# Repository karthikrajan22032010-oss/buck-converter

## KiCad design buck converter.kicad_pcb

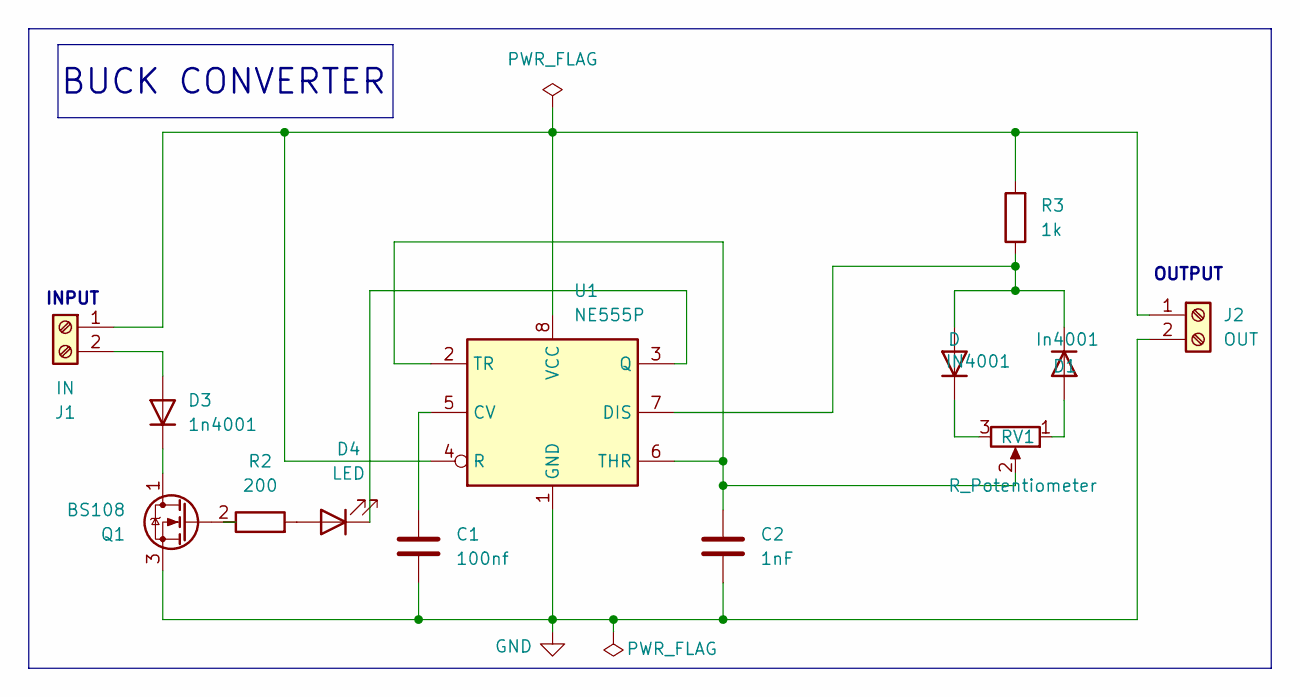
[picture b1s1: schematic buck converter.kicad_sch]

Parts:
C1: 100nf; C_Disc_D8.0mm_W5.0mm_P7.50mm
C2: 1nF; C_Disc_D8.0mm_W5.0mm_P7.50mm
D1: In4001; D_5W_P12.70mm_Horizontal
D3: 1n4001; D_5W_P12.70mm_Horizontal
D4: LED; LED_D5.0mm
IN4001: D; D_5W_P12.70mm_Horizontal
J1: IN; TerminalBlock_Phoenix_MKDS-1,5-2_1x02_P5.00mm_Horizontal
J2: OUT; TerminalBlock_Phoenix_MKDS-1,5-2_1x02_P5.00mm_Horizontal
Q1: BS108; TO-92_Inline_Wide
R2: 200; R_Axial_DIN0207_L6.3mm_D2.5mm_P7.62mm_Horizontal
R3: 1k; R_Axial_DIN0207_L6.3mm_D2.5mm_P7.62mm_Horizontal
RV1: R_Potentiometer; Potentiometer_Alps_RK09Y11_Single_Horizontal
U1: NE555P; DIP-8_W7.62mm

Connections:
GND: C1.2, C2.2, J2.2, Q1.3 (S), U1.1 (GND)
unnamed: D1.2 (A), RV1.1
unnamed: D1.1 (K), IN4001.2 (A), R3.1, U1.7 (DIS)
unnamed: D3.2 (A), J1.2
unnamed: D3.1 (K), Q1.1 (D)
unnamed: D4.2 (A), R2.2
unnamed: D4.1 (K), U1.3 (Q)
unnamed: IN4001.1 (K), RV1.3
unnamed: J1.1, J2.1, R3.2, U1.4 (R), U1.8 (VCC)
unnamed: Q1.2 (G), R2.1
unnamed: C1.1, U1.5 (CV)
unnamed: C2.1, RV1.2, U1.2 (TR), U1.6 (THR)

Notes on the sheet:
BUCK CONVERTER
OUTPUT
INPUT

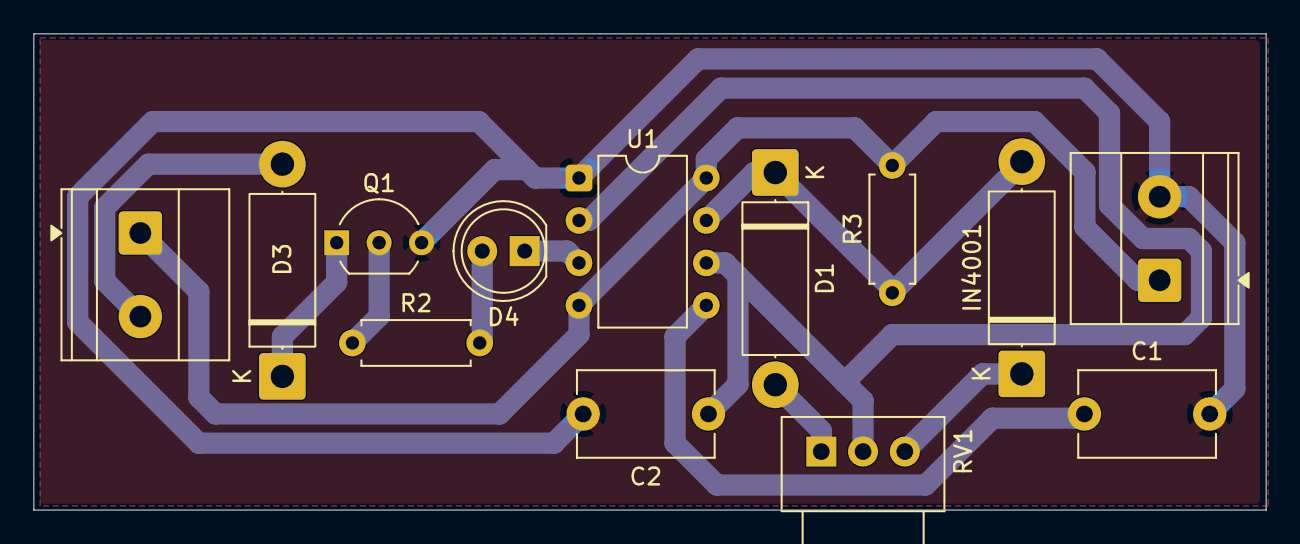
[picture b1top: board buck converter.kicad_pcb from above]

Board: 2 copper layers, 73.8 x 28.5 mm, 13 parts (0 on the bottom side), 12 nets.
